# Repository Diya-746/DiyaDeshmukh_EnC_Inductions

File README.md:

# Diya Deshmukh – Kratos EnC Inductions

## Repository Structure

```
src/
├── kratos_diya
├── kratos_diya_msgs
└── arm_humble
```

---

# Week 3 part 1

## Question 1

Implemented ROS2 publisher and subscriber nodes for rover monitoring.

Features:

- Publisher
- Subscriber
- Launch file
- Custom message
- ROS2 package

---

# Week 3 part 2

## Question 1

Solved Forward and Inverse Kinematics for the given planar manipulator.

## Question 2

Implemented an Inverse Kinematics controller for the provided robotic arm.

### Features

- Publishes `sensor_msgs/msg/JointState`
- Controls
  - base_yaw_joint
  - shoulder_joint
  - elbow_joint
- Computes inverse kinematics
- Rejects unreachable targets
- Maintains internal end-effector position

---

## Assumptions

- Wrist and gripper remain fixed.
- Link lengths taken from the provided URDF.

---

## Challenges

- ROS2 package setup
- Custom message creation
- RViz visualization
- ROS2 launch configuration
- Package dependency debugging

---

## Testing

Verified using:

- `ros2 topic echo /joint_states`
- RViz visualization
- Reachability checks
- Successful movement of robotic arm# DiyaDeshmukh_EnC_Inductions

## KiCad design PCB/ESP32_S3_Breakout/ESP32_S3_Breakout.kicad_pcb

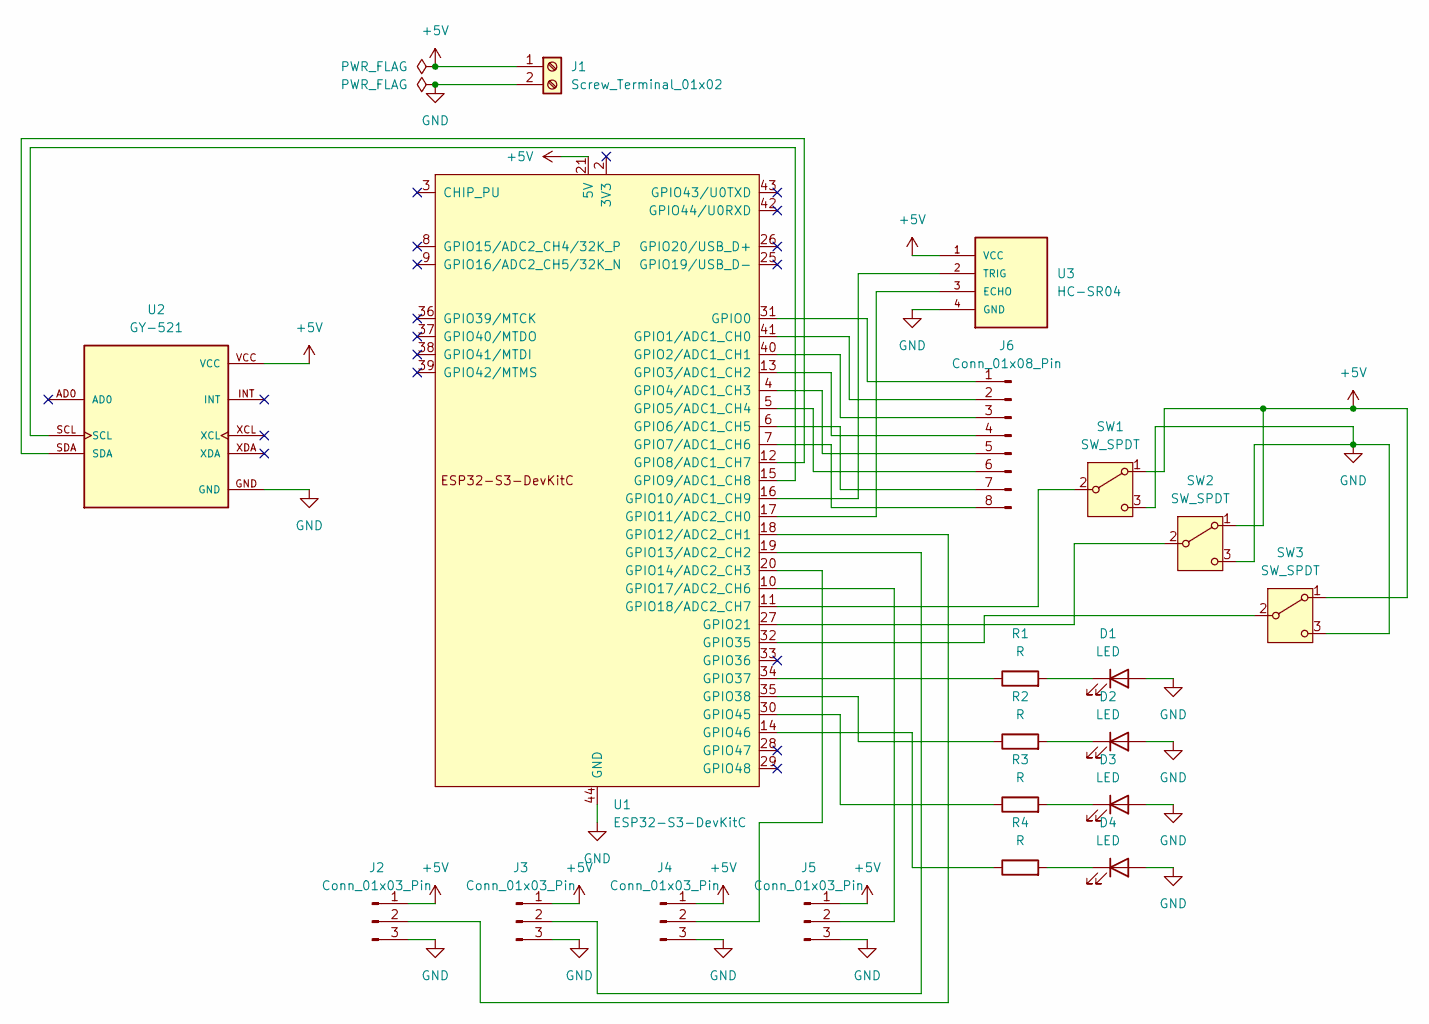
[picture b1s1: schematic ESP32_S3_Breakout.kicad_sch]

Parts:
D1, D2, D3, D4: LED; LED_D5.0mm
J1: Screw_Terminal_01x02; TerminalBlock_bornier-2_P5.08mm
J2, J3, J4, J5: Conn_01x03_Pin; PinHeader_1x03_P2.54mm_Vertical
J6: Conn_01x08_Pin; PinHeader_1x08_P2.54mm_Vertical
R1, R2, R3, R4: R; R_Axial_DIN0207_L6.3mm_D2.5mm_P10.16mm_Horizontal
SW1, SW2, SW3: SW_SPDT; SW_E-Switch_EG1271_SPDT
U1: ESP32-S3-DevKitC
U2: GY-521; MODULE_GY-521; PARTREV NA
U3: HC-SR04; XCVR_HC-SR04

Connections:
+5V: J1.1, J2.1, J3.1, J4.1, J5.1, SW1.1 (A), SW2.1 (A), SW3.1 (A), U1.21 (5V), U2.VCC, U3.1 (VCC)
GND: D1.2 (A), D2.2 (A), D3.2 (A), D4.2 (A), J1.2, J2.3, J3.3, J4.3, J5.3, SW1.3 (C), SW2.3 (C), SW3.3 (C), U1.22 (GND), U1.23 (GND), U1.24 (GND), U1.44 (GND), U2.GND, U3.4 (GND)
unnamed: D1.1 (K), R1.2
unnamed: D2.1 (K), R2.2
unnamed: D3.1 (K), R3.2
unnamed: D4.1 (K), R4.2
unnamed: J2.2, U1.18 (GPIO12/ADC2_CH1)
unnamed: J3.2, U1.19 (GPIO13/ADC2_CH2)
unnamed: J4.2, U1.20 (GPIO14/ADC2_CH3)
unnamed: J5.2, U1.10 (GPIO17/ADC2_CH6)
unnamed: J6.1, U1.31 (GPIO0)
unnamed: J6.2, U1.41 (GPIO1/ADC1_CH0)
unnamed: J6.3, U1.40 (GPIO2/ADC1_CH1)
unnamed: J6.4, U1.13 (GPIO3/ADC1_CH2)
unnamed: J6.5, U1.4 (GPIO4/ADC1_CH3)
unnamed: J6.6, U1.5 (GPIO5/ADC1_CH4)
unnamed: J6.7, U1.6 (GPIO6/ADC1_CH5)
unnamed: J6.8, U1.7 (GPIO7/ADC1_CH6)
unnamed: SW1.2 (B), U1.11 (GPIO18/ADC2_CH7)
unnamed: SW2.2 (B), U1.27 (GPIO21)
unnamed: SW3.2 (B), U1.32 (GPIO35)
unnamed: U1.12 (GPIO8/ADC1_CH7), U2.SDA
unnamed: U1.15 (GPIO9/ADC1_CH8), U2.SCL
unnamed: U1.16 (GPIO10/ADC1_CH9), U3.2 (TRIG)
unnamed: U1.17 (GPIO11/ADC2_CH0), U3.3 (ECHO)
unnamed: R1.1, U1.34 (GPIO37)
unnamed: R2.1, U1.35 (GPIO38)
unnamed: R3.1, U1.30 (GPIO45)
unnamed: R4.1, U1.14 (GPIO46)

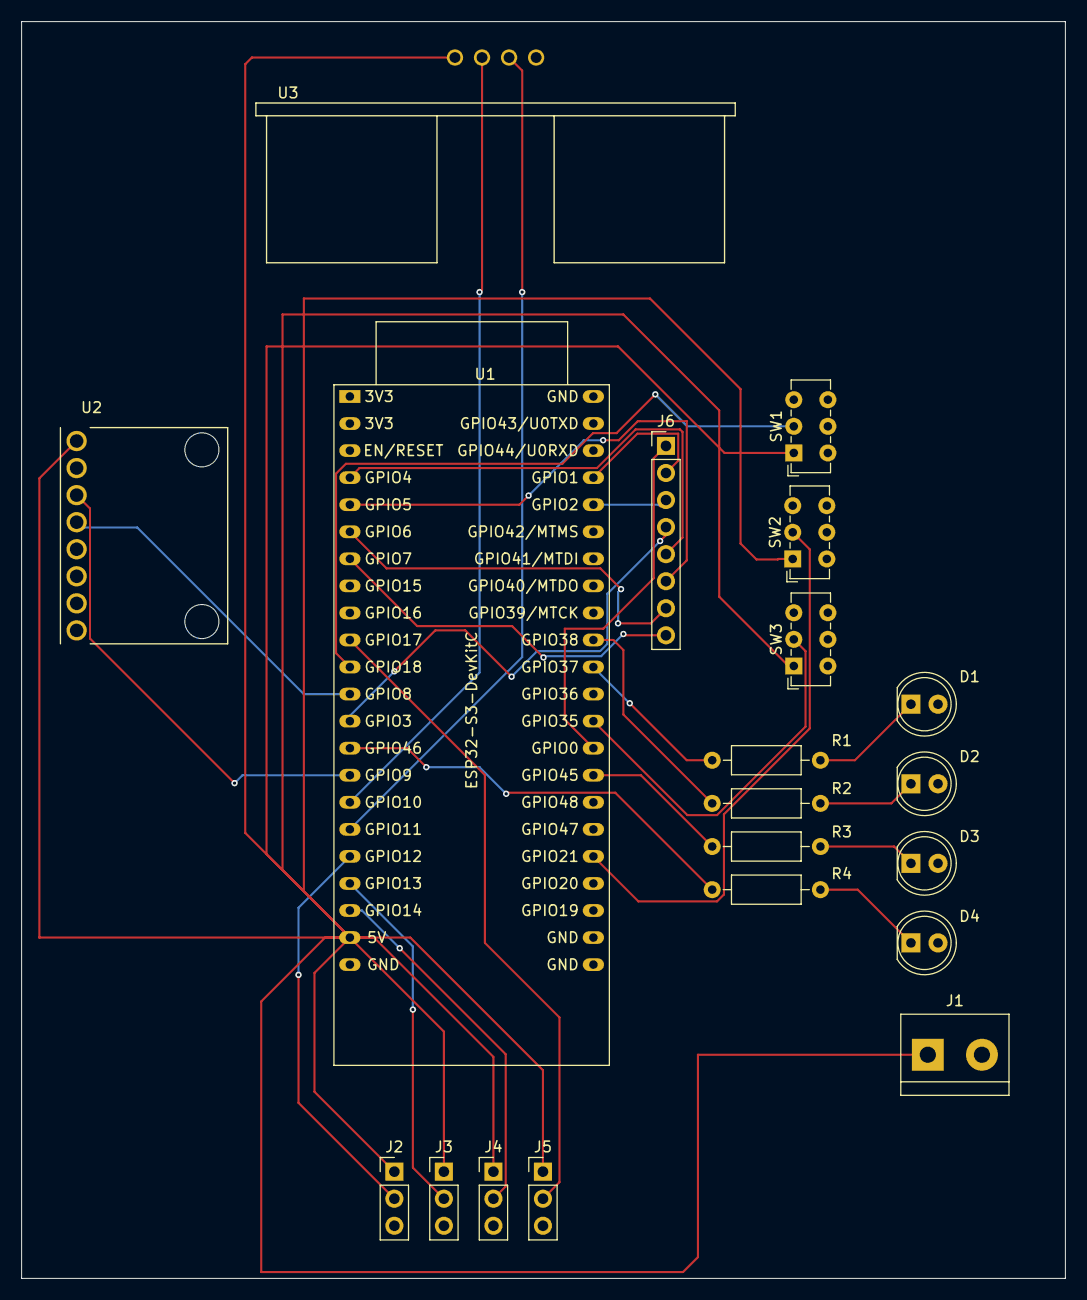
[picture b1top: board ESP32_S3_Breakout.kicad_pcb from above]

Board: 2 copper layers, 98.0 x 118.0 mm, 20 parts (0 on the bottom side), 29 nets.

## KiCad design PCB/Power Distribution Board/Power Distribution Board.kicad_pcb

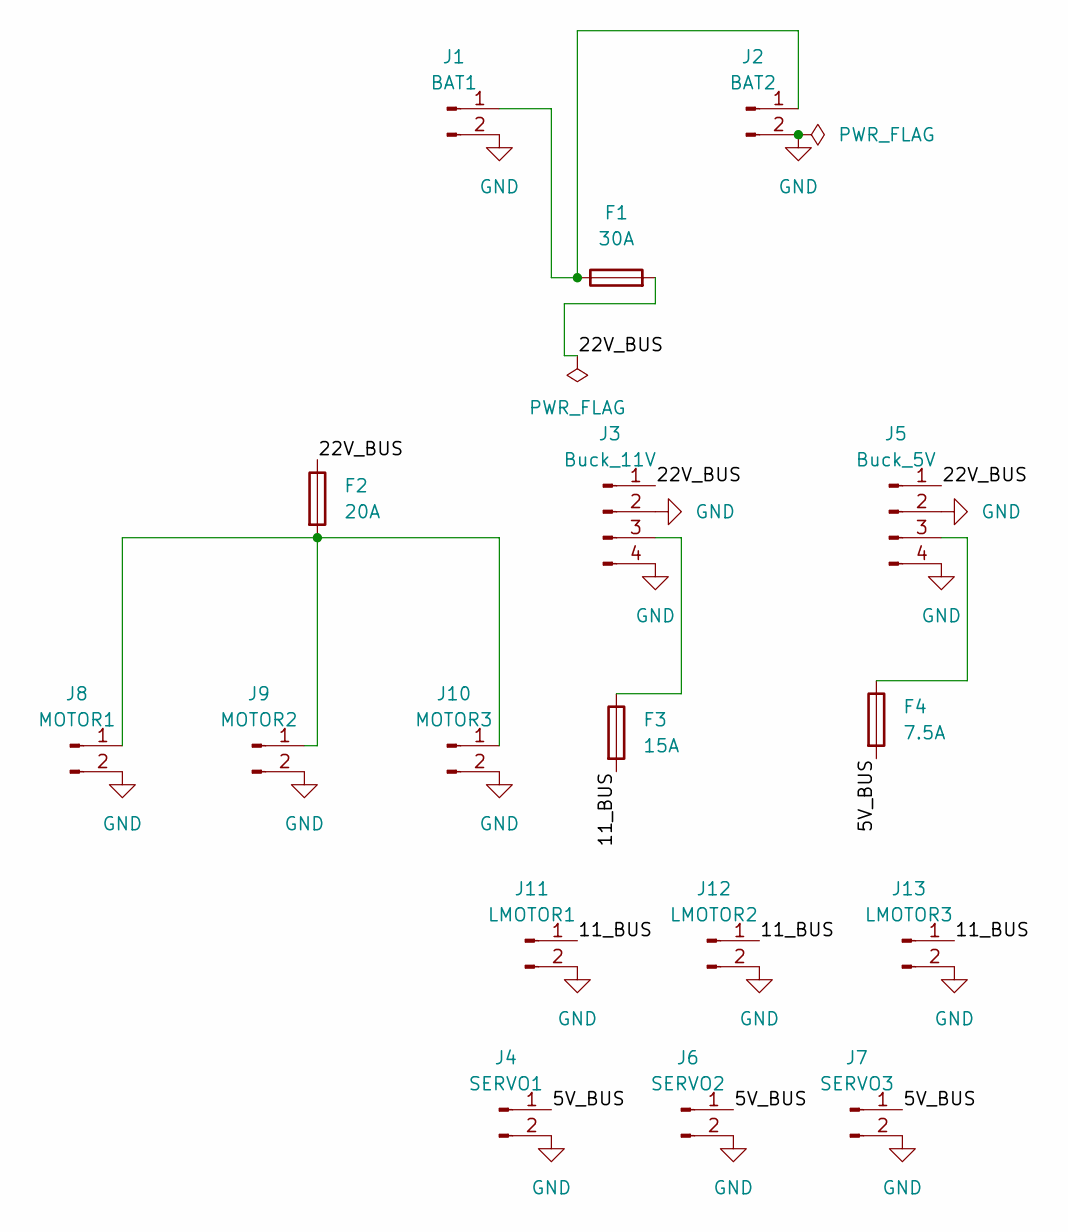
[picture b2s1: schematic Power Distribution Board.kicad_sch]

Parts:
F1: 30A; Fuse_Blade_Mini_directSolder
F2: 20A; Fuse_Blade_Mini_directSolder
F3: 15A; Fuse_Blade_Mini_directSolder
F4: 7.5A; Fuse_Blade_Mini_directSolder
J1: BAT1; AMASS_XT60-M_1x02_P7.20mm_Vertical
J2: BAT2; AMASS_XT60-M_1x02_P7.20mm_Vertical
J3: Buck_11V; Buck20A
J4: SERVO1; TerminalBlock_MaiXu_MX126-5.0-02P_1x02_P5.00mm
J5: Buck_5V; Buck5A
J6: SERVO2; TerminalBlock_MaiXu_MX126-5.0-02P_1x02_P5.00mm
J7: SERVO3; TerminalBlock_MaiXu_MX126-5.0-02P_1x02_P5.00mm
J8: MOTOR1; TerminalBlock_bornier-2_P5.08mm
J9: MOTOR2; TerminalBlock_bornier-2_P5.08mm
J10: MOTOR3; TerminalBlock_bornier-2_P5.08mm
J11: LMOTOR1; TerminalBlock_MaiXu_MX126-5.0-02P_1x02_P5.00mm
J12: LMOTOR2; TerminalBlock_MaiXu_MX126-5.0-02P_1x02_P5.00mm
J13: LMOTOR3; TerminalBlock_MaiXu_MX126-5.0-02P_1x02_P5.00mm

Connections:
/5V_BUS: F4.2, J4.1, J6.1, J7.1
/11_BUS: F3.2, J11.1, J12.1, J13.1
/22V_BUS: F1.2, F2.1, J3.1, J5.1
GND: J1.2, J2.2, J3.2, J3.4, J4.2, J5.2, J5.4, J6.2, J7.2, J8.2, J9.2, J10.2, J11.2, J12.2, J13.2
unnamed: F1.1, J1.1, J2.1
unnamed: F3.1, J3.3
unnamed: F4.1, J5.3
unnamed: F2.2, J8.1, J9.1, J10.1

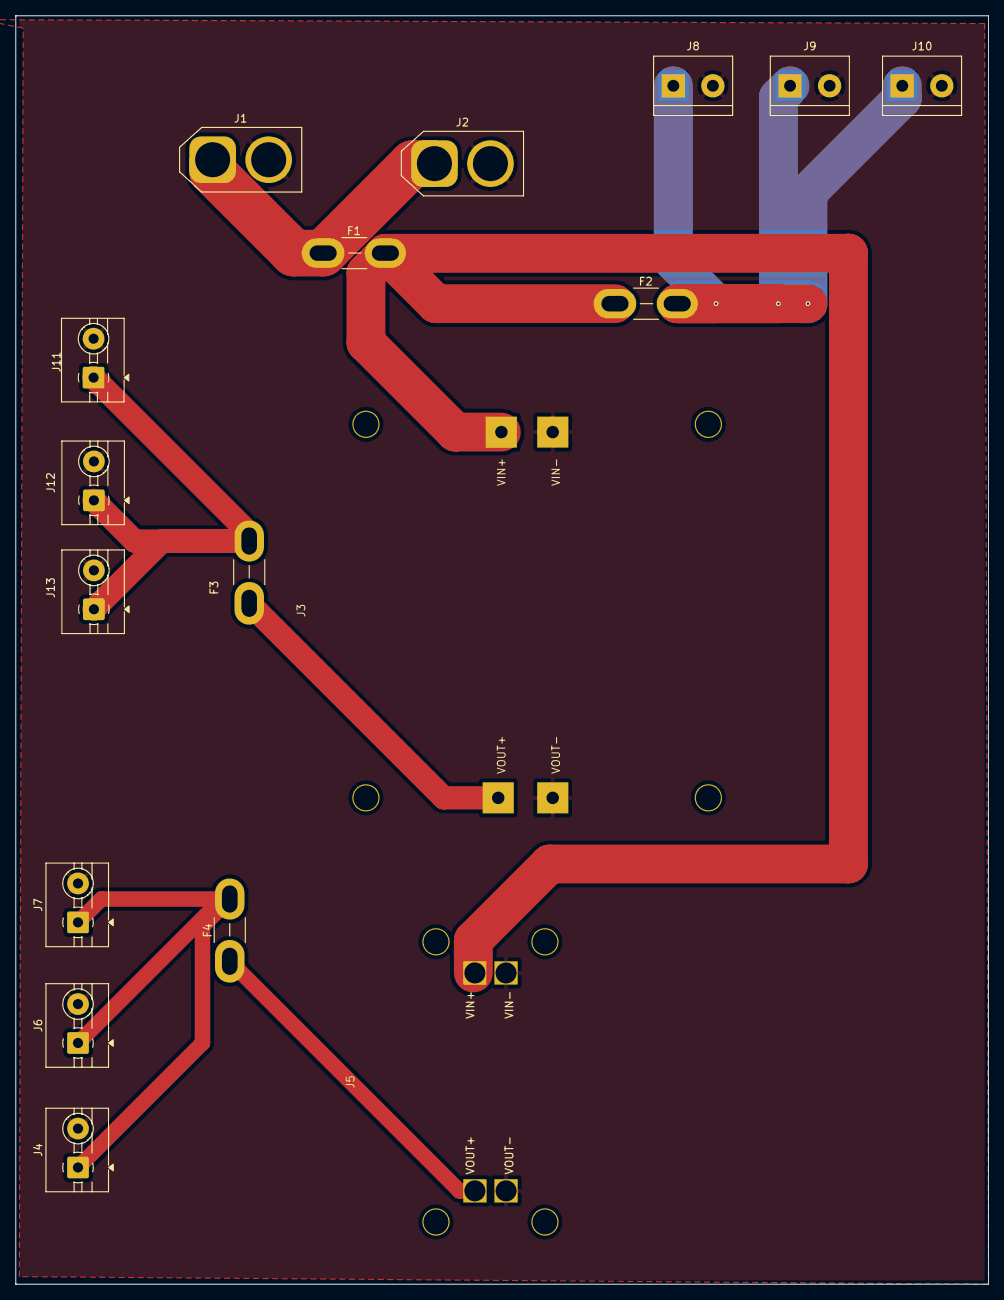
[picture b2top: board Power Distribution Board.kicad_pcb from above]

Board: 2 copper layers, 125.0 x 163.0 mm, 17 parts (0 on the bottom side), 8 nets.
